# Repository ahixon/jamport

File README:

Eagle designs and Gerber files for a Mac G4 modem to serial port adapter.

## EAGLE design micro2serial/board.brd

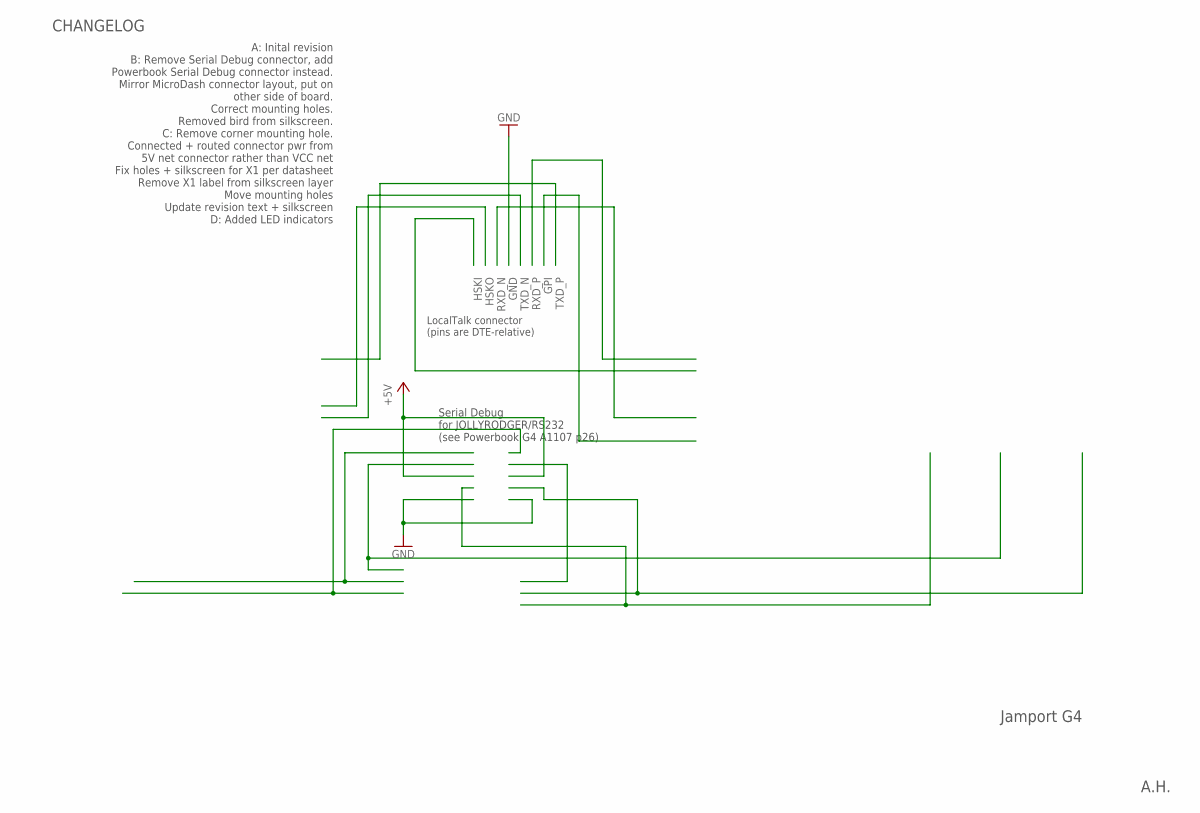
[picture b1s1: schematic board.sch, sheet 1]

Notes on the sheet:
A.H.
Jamport G4
LocalTalk connector (pins are DTE-relative)
Serial Debug for JOLLYRODGER/RS232 (see Powerbook G4 A1107 p26)
A: Inital revision B: Remove Serial Debug connector, add Powerbook Serial Debug connector instead. Mirror MicroDash connector layout, put on other side of board. Correct mounting holes. Removed bird from silkscreen. C: Remove corner mounting hole. Connected + routed connector pwr from 5V net connec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
CHANGELOG

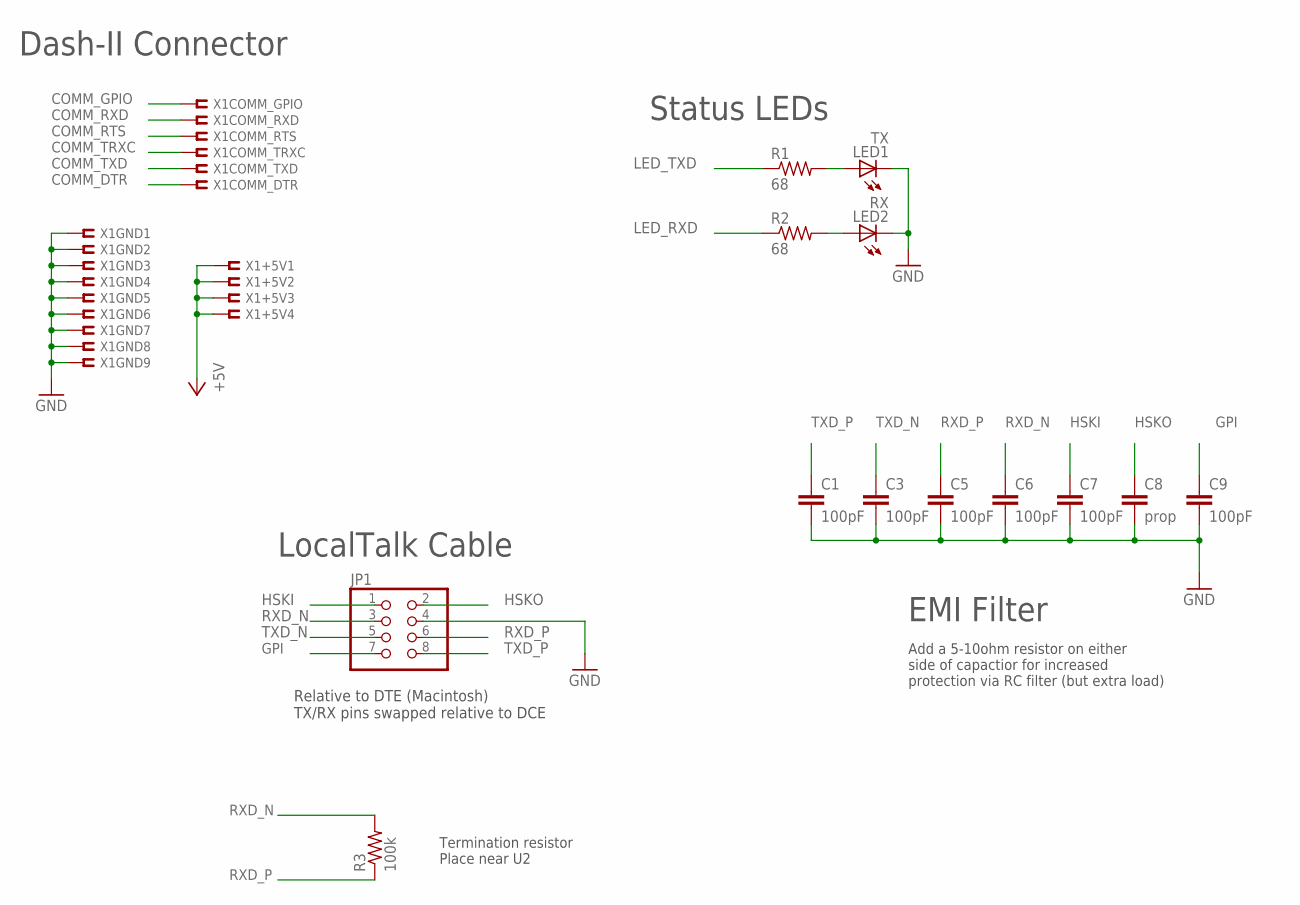
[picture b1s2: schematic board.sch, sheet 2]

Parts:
C1, C3, C5, C6, C7, C9: 100pF; C0603
C8: prop; C0603
JP1: PINHD-2X4; 2X04
LED1: TX; CHIPLED_1305
LED2: RX; CHIPLED_1305
R1, R2: 68; R0603
R3: 100k; R0603
X1: 55091-0409REV; 55091-0409-REV

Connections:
+5V: X1.37, X1.38, X1.39, X1.40; also elsewhere on the board
COMM_DTR: X1.9; also elsewhere on the board
COMM_GPIO: X1.12; also elsewhere on the board
COMM_RTS: X1.6
COMM_RXD: X1.10; also elsewhere on the board
COMM_TRXC: X1.15; also elsewhere on the board
COMM_TXD: X1.13; also elsewhere on the board
GND: C1.2, C3.2, C5.2, C6.2, C7.2, C8.2, C9.2, JP1.4, LED1.C, LED2.C, X1.8, X1.11, X1.14, X1.17, X1.22, X1.25, X1.28, X1.31, X1.33; also elsewhere on the board
GPI: C9.1, JP1.7; also elsewhere on the board
HSKI: C7.1, JP1.1; also elsewhere on the board
HSKO: C8.1, JP1.2; also elsewhere on the board
LED_RXD: R2.1; also elsewhere on the board
LED_TXD: R1.1; also elsewhere on the board
unnamed: LED2.A, R2.2
unnamed: LED1.A, R1.2
RXD_N: C6.1, JP1.3, R3.2; also elsewhere on the board
RXD_P: C5.1, JP1.6, R3.1; also elsewhere on the board
TXD_N: C3.1, JP1.5; also elsewhere on the board
TXD_P: C1.1, JP1.8; also elsewhere on the board

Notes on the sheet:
LocalTalk Cable
Relative to DTE (Macintosh) TX/RX pins swapped relative to DCE
Dash-II Connector
Status LEDs
EMI Filter
Termination resistor Place near U2
Add a 5-10ohm resistor on either side of capactior for increased protection via RC filter (but extra load)

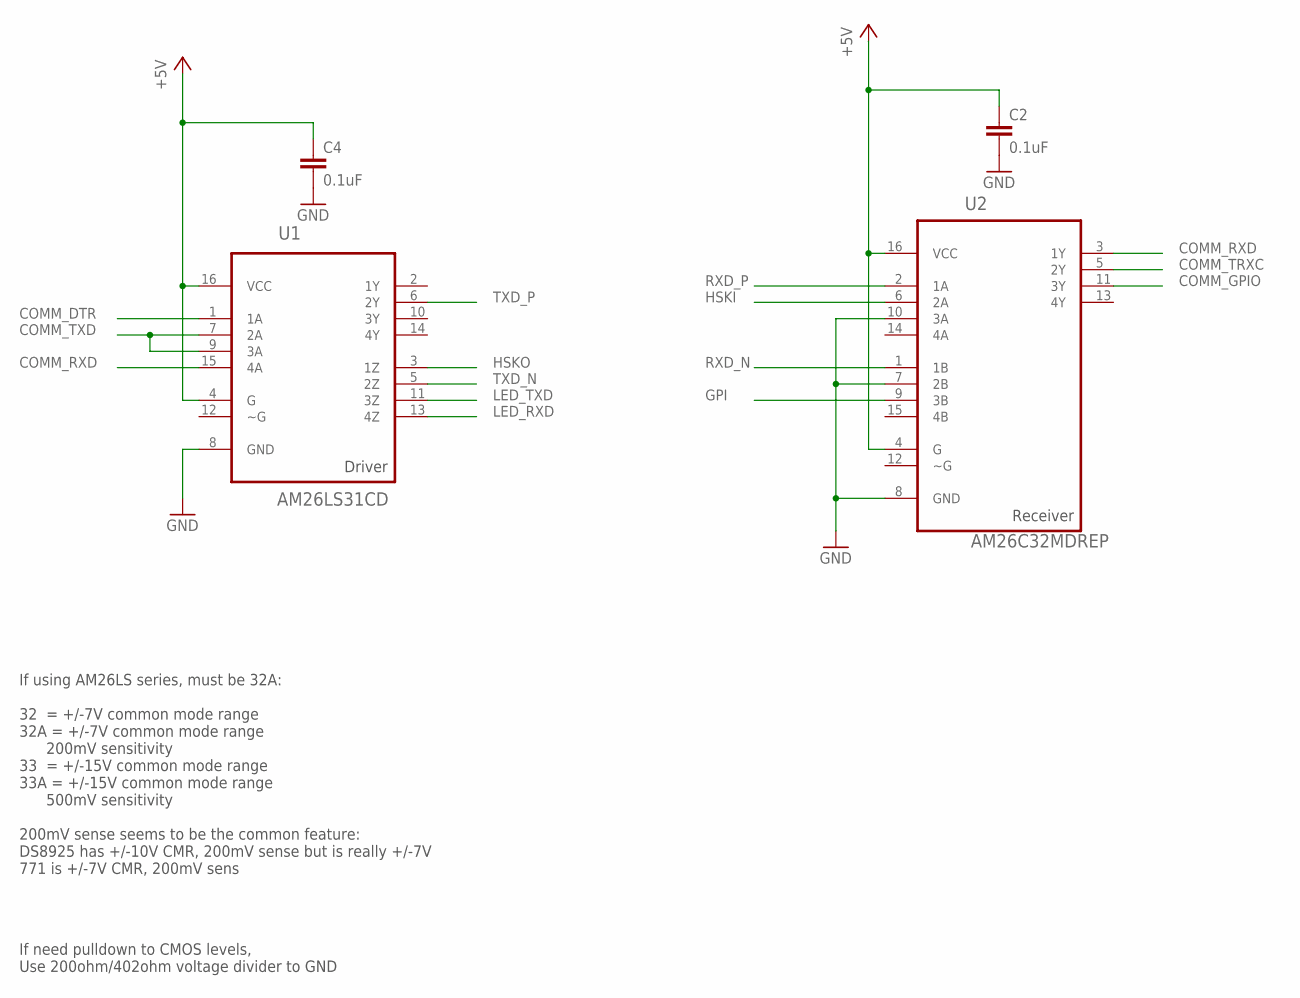
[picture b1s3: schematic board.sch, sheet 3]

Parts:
C2, C4: 0.1uF; C0603
U1: AM26LS31CD; SOIC127P600X175-16N
U2: AM26C32MDREP; SOIC127P600X175-16N

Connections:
+5V: C2.1, C4.1, U1.4 (G), U1.16 (VCC), U2.4 (G), U2.16 (VCC); also elsewhere on the board
COMM_DTR: U1.1 (1A); also elsewhere on the board
COMM_GPIO: U2.11 (3Y); also elsewhere on the board
COMM_RXD: U1.15 (4A), U2.3 (1Y); also elsewhere on the board
COMM_TRXC: U2.5 (2Y); also elsewhere on the board
COMM_TXD: U1.7 (2A), U1.9 (3A); also elsewhere on the board
GND: C2.2, C4.2, U1.8 (GND), U2.7 (2B), U2.8 (GND), U2.10 (3A); also elsewhere on the board
GPI: U2.9 (3B); also elsewhere on the board
HSKI: U2.6 (2A); also elsewhere on the board
HSKO: U1.3 (1Z); also elsewhere on the board
LED_RXD: U1.13 (4Z); also elsewhere on the board
LED_TXD: U1.11 (3Z); also elsewhere on the board
RXD_N: U2.1 (1B); also elsewhere on the board
RXD_P: U2.2 (1A); also elsewhere on the board
TXD_N: U1.5 (2Z); also elsewhere on the board
TXD_P: U1.6 (2Y); also elsewhere on the board

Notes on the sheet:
Driver
Receiver
If need pulldown to CMOS levels, Use 200ohm/402ohm voltage divider to GND
If using AM26LS series, must be 32A: 32 = +/-7V common mode range 32A = +/-7V common mode range 200mV sensitivity 33 = +/-15V common mode range 33A = +/-15V common mode range 500mV sensitivity 200mV sense seems to be the common feature: DS8925 has +/-10V CMR, 200mV sense but is really +/-7V 771 is 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

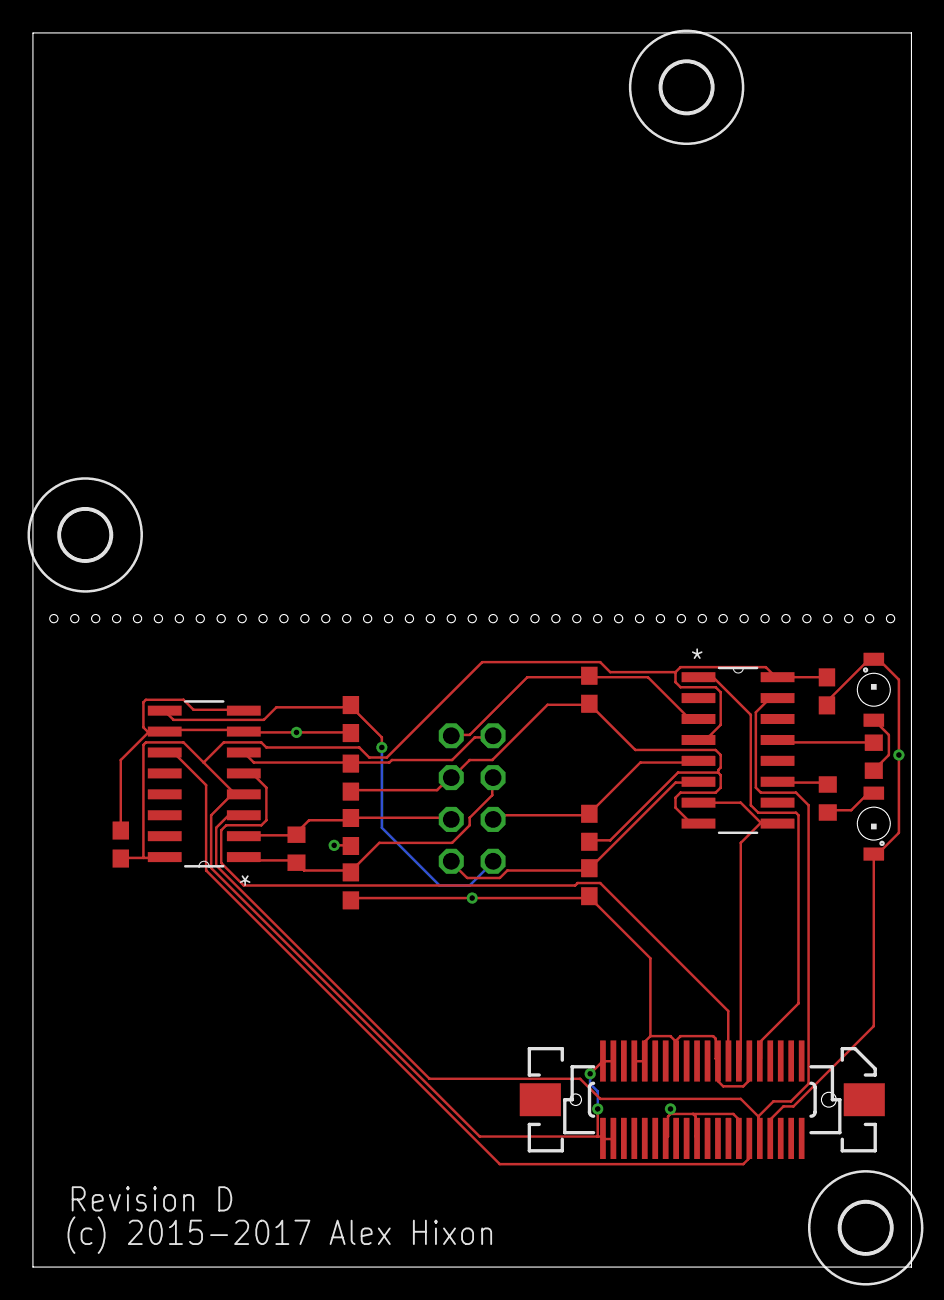
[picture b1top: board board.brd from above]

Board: 2 copper layers, 53.3 x 74.9 mm, 21 parts (1 on the bottom side), 18 nets.

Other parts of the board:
U$1, U$2, U$3: 3,0

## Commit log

2024-08-28 friendship ended with .DS_Store
2024-08-28 add LICENSE
2024-08-28 LICENSE -> README
2024-09-08 updat readme
2025-07-18 Update LICENSE
    Replace with an actual LICENSE.

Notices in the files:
micro2serial/board.brd:
(c) 2015-2017 Alex Hixon
